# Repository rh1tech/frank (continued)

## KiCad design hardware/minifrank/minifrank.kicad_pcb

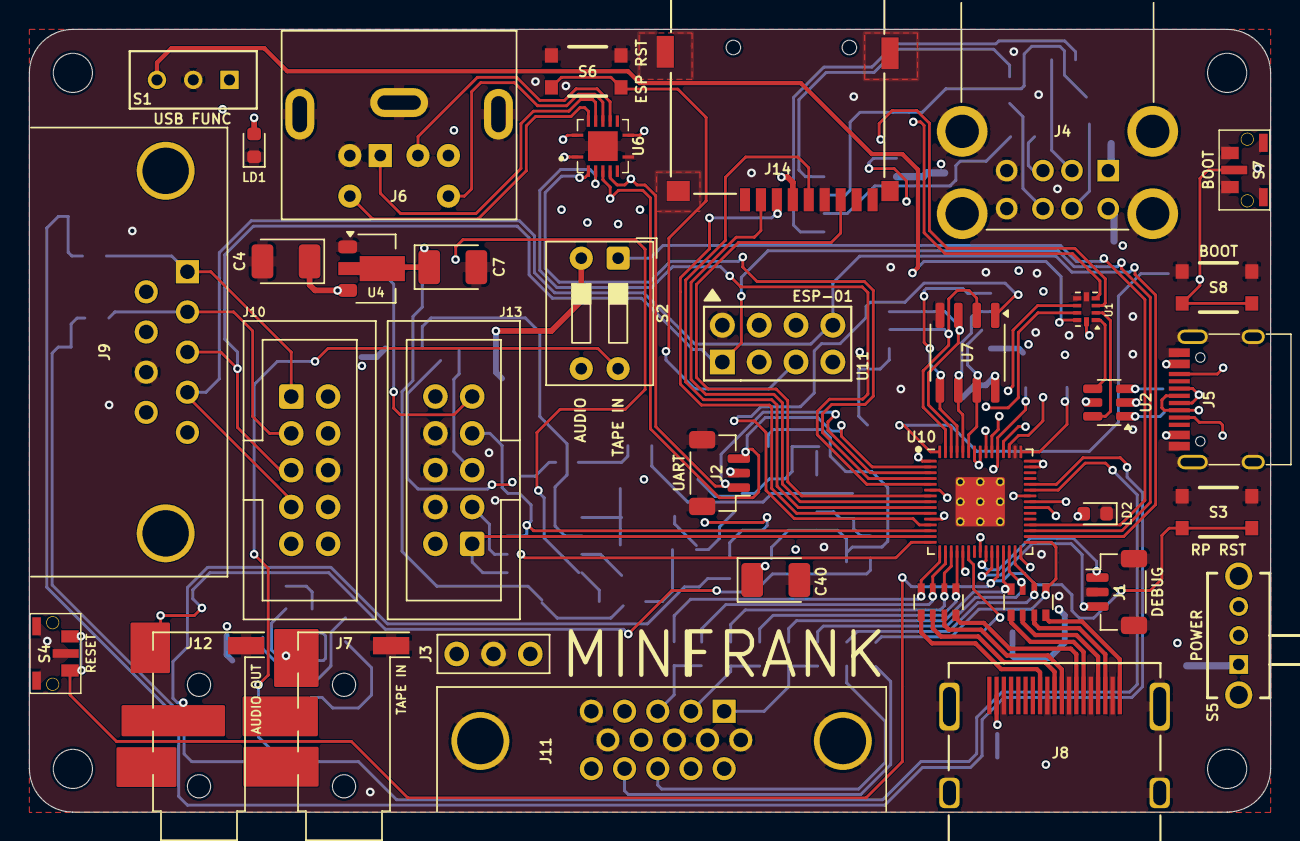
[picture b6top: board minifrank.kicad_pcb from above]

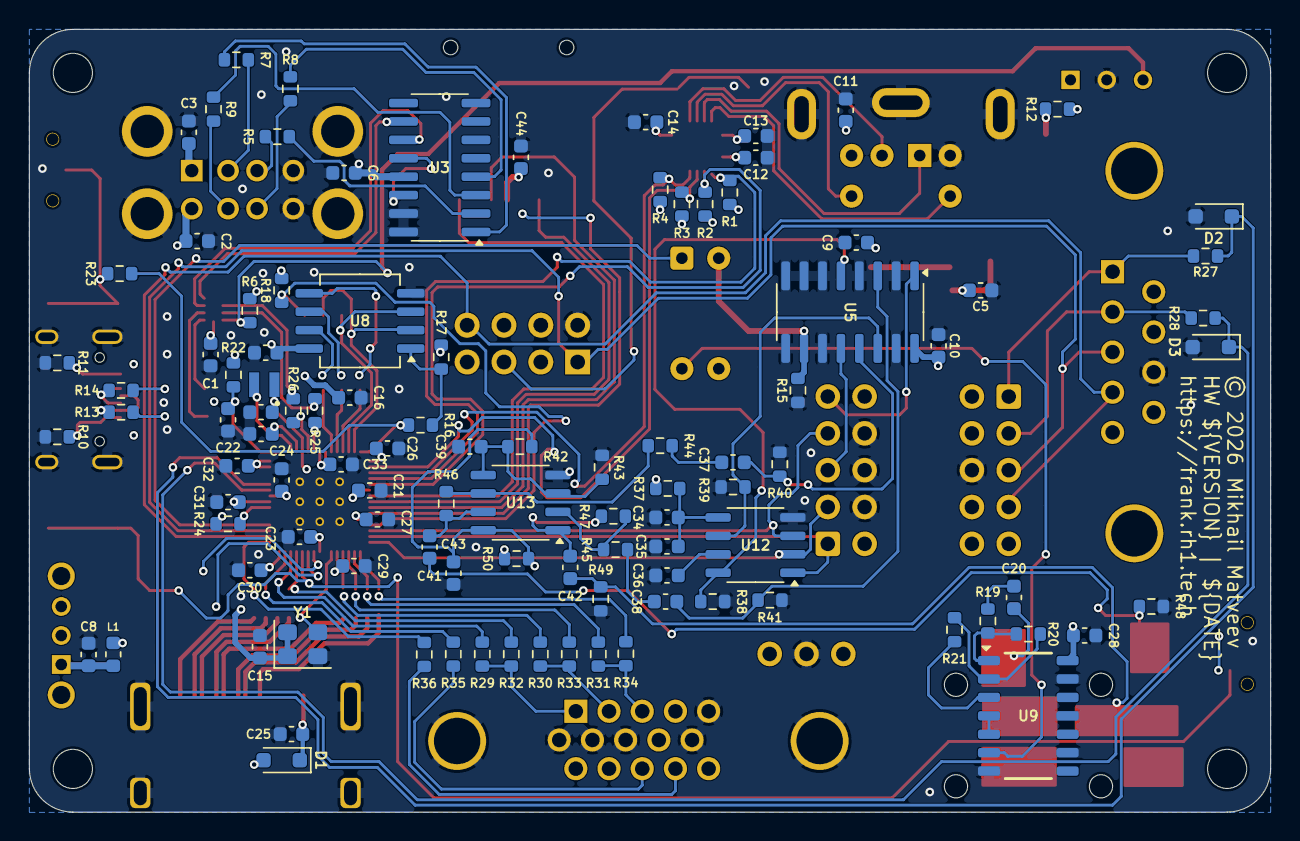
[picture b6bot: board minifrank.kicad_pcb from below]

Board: 4 copper layers, 85.6 x 54.0 mm, 143 parts (103 on the bottom side), 119 nets.

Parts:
C1, C5, C8, C9, C10, C11, C12, C13, C14, C15, C16, C17, C20, C21, C24, C25, C26, C27, C28, C29, C30, C31, C32, C33, C35, C43, C44: 100n; C_0603_1608Metric
C2, C3, C34, C36, C37, C38, C39, C41, C42: 10u; C_0603_1608Metric
C4, C7: 22u; CP_EIA-3528-12_Kemet-T
C6, C18, C19, C22, C23: 4.7u; C_0603_1608Metric
C40: 10u; CP_EIA-3528-12_Kemet-T
D1: 1N5819WS; D_SOD-323
D2, D3: 3V3; D_SOD-323
H1, H2, H3, H4: Hole 2.7mm; MountingHole_2.7mm
J1: DEBUG; JST_SH_BM03B-SRSS-TB_1x03-1MP_P1.00mm_Vertical
J2: UART; JST_SH_BM03B-SRSS-TB_1x03-1MP_P1.00mm_Vertical
J3: PWR; PinHeader_1x03_P2.54mm
J4: SS-52100-004; USB_A_Stacked
J5: USB4215-03-A; USB_C_Receptacle
J6: MDC-036; MiniDIN_6pin_Female
J7: PJ-320D; AudioJack_3.5mm_PJ320D_TapeIn
J8: HDMI-001 19PCBTP; HDMI_Female
J9: GP2; DSUB-9_Male_TopMount
J10: Conn_02x05_Top_Bottom; IDC-Header_2x05_P2.54mm_Vertical
J11: VGA; DSUB-15_Female
J12: PJ-320D; AudioJack_3.5mm_PJ320D_AudioOut
J13: Ext_Sound; IDC-Header_2x05_P2.54mm_Vertical
J14: 104031-0811; MicroSD_SMD_Long
L1: 330R; L_0603_1608Metric
L2: 3.3u; L_pol_2016
LD1: Green; LED_0603_1608Metric
LD2: Blue; LED_0603_1608Metric
R1, R2, R3, R4, R6, R15, R17, R18, R40, R41, R42, R43, R44, R45: 10K; R_0603_1608Metric
R5, R7, R8, R9, R13, R14: 22R; R_0603_1608Metric
R10, R11: 5.1K; R_0603_1608Metric
R12, R23, R24, R27, R28, R32, R33, R34: 1K; R_0603_1608Metric
R16: 0R; R_0603_1608Metric
R19: 4.7K; R_0603_1608Metric
R20, R21: 100K; R_0603_1608Metric
R22: 33R; R_0603_1608Metric
R25, R26: 27R; R_0603_1608Metric
R29, R30, R31: 330R; R_0603_1608Metric
R35, R36, R37, R50: 100R; R_0603_1608Metric
R38, R39: 470R; R_0603_1608Metric
R46, R47: 47K; R_0603_1608Metric
R48, R49: 20K; R_0603_1608Metric
RN1, RN2: 270R; R_Array_4x0603
S1: SS12D00; Switch_Slide_SS12D00
S2: SW_DIP_x02; SW_DIP_SPSTx02_Slide_9.78x7.26mm_W7.62mm_P2.54mm
S3, S8: RP Reset; KMR_2
S4, S7: RP Reset; TS-1234VW
S5: SK12D07VG3NS
S6: ESP Reset; KMR_2
U1: TS3USB221RSER; UQFN-10
U2: USBLC6-2SC6; SOT-23-6
U3: MW7211A; SOP-16
U4: AMS1117-3.3; SOT-89-3
U5: 74HC4052D; SOP-16_P1.27mm
U6: TXS0104ERGYR; RGY_S-PVQFN-N14_
U7: ESP-PSRAM64H; SO-8
U8: W25Q128JVS; SOIC-8
U9: CD4069UBM; SOIC127P600X175-14N
U10: RP2350; QFN-60_RP2350A
U11: ESP-01v090; ESP-01
U12: TDA1387T; SO-8
U13: LM358; SO-8
Y1: ASE-12MHz; Oscillator_SMD_Abracon_ASE-4Pin_3.2x2.5mm

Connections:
+1V1: C19.1, C21.1, C23.1, C24.1, L2.1, U10.6 (DVDD), U10.23 (DVDD), U10.39 (DVDD), U10.50 (VREG_FB)
+3V3: C1.2, C7.1, C9.2, C12.1, C14.1, C15.1, C16.1, C17.1, C18.1, C26.1, C27.1, C28.1, C29.1, C30.1, C31.1, C32.1, C33.1, C44.2, J3.1, J13.10, J14.4 (VDD), R1.2, R2.2, R3.2, R4.2, R6.1, R12.2, R17.1, R18.2, R22.1, U1.10 (VCC), U4.2 (VO), U6.1 (VCCA), U6.8 (OE), U7.8 (VCC), U8.8 (VCC), U9.14 (VDD), U10.1 (IOVDD), U10.11 (IOVDD), U10.20 (IOVDD), U10.30 (IOVDD), U10.38 (IOVDD), U10.44 (ADC_AVDD), U10.45 (IOVDD), U10.49 (VREG_VIN), U10.53 (USB_OTP_VDD), U10.54 (QSPI_IOVDD), U11.7 (VCC), Y1.1 (EN), Y1.4 (Vdd)
/Audio Multiplexer/AMP_IN_L: C37.1, R40.1, U5.13 (1Z)
/Audio Multiplexer/AMP_IN_R: C38.1, R41.1, U5.3 (2Z)
/Audio Multiplexer/AUDIOSW: R15.2, S2.2, U5.10 (S0)
/Audio Multiplexer/TDA_L: R39.2, U5.14 (1Y1), U12.6 (A_LEFT)
/Audio Multiplexer/TDA_R: R38.1, U5.5 (2Y1), U12.8 (A_RIGHT)
/Audio Multiplexer/TS_OUT_L: J13.3, U5.12 (1Y0)
/Audio Multiplexer/TS_OUT_R: J13.5, U5.1 (2Y0)
/Audio/AMP_OUTL: C41.2, J12.T, R48.2
/Audio/AMP_OUTR: C42.2, J12.R, R49.2
/D+: R25.1, U1.8 (D+)
/D-: R26.1, U1.7 (D-)
/ESP_RST: S6.2, S6.4, U11.5 (RST)
/GPIO0: J2.1, R3.1, U6.4 (A3), U10.2 (GPIO0)
/GPIO1: J2.3, R4.1, U6.5 (A4), U10.3 (GPIO1)
/GPIO2: R1.1, U6.2 (A1), U10.4 (GPIO2)
/GPIO3: R2.1, U6.3 (A2), U10.5 (GPIO3)
/GPIO4: J14.7 (DAT0), U10.7 (GPIO4)
/GPIO5: J14.2 (DAT3/CD), U10.8 (GPIO5)
/GPIO6: J14.5 (CLK), U10.9 (GPIO6)
/GPIO7: J14.3 (CMD), U10.10 (GPIO7)
/GPIO9: J13.4, U10.13 (GPIO9), U12.3 (DATA)
/GPIO10: J13.1, U10.14 (GPIO10), U12.1 (SCLK)
/GPIO11: J13.2, U10.15 (GPIO11), U12.2 (LRCK)
/GPIO12: R34.1, RN1.4 (R4.1), U10.16 (GPIO12)
/GPIO13: R31.1, RN1.3 (R3.1), U10.17 (GPIO13)
/GPIO14: R33.1, RN1.2 (R2.1), U10.18 (GPIO14)
/GPIO15: R30.1, RN1.1 (R1.1), U10.19 (GPIO15)
/GPIO16: R32.1, RN2.4 (R4.1), U10.27 (GPIO16)
/GPIO17: R29.1, RN2.3 (R3.1), U10.28 (GPIO17)
/GPIO18: R35.2, RN2.2 (R2.1), U10.29 (GPIO18)
/GPIO19: R36.2, RN2.1 (R1.1), U10.31 (GPIO19)
/GPIO20: J9.4, J10.4, U10.32 (GPIO20), U11.8 (URXD)
/GPIO21: J9.3, J10.3, U10.33 (GPIO21), U11.1 (UTXD)
/GPIO22: S2.1, U10.34 (GPIO22)
/GPIO26: D3.1 (K), R28.1, U10.40 (GPIO26_ADC0)
/GPIO27: D2.1 (K), R27.1, U10.41 (GPIO27_ADC1)
/Gamepad/G_DATA1: J9.2, J10.2, R28.2
/Gamepad/G_DATA2: J9.1, J10.1, R27.2
/PS2/KB_CLK_5V: J6.5, U6.13 (B1)
/PS2/KB_DATA_5V: J6.1, U6.12 (B2)
/PS2/MS_CLK_5V: J6.6, U6.11 (B3)
/PS2/MS_DATA_5V: J6.2, U6.10 (B4)
/Power/D1+: U1.1 (1D+), U2.4 (I/O2)
/Power/D1-: U1.2 (1D-), U2.6 (I/O1)
/Power/D2+: U1.3 (2D+), U3.11 (DPU)
/Power/D2-: U1.4 (2D-), U3.10 (DMU)
/Power/DS1+: R5.1, U3.2 (DP0)
/Power/DS1-: R7.1, U3.1 (DM0)
/Power/DS2+: R8.1, U3.4 (DP1)
/Power/DS2-: R9.1, U3.3 (DM1)
/Power/VBUS_IN: J5.2 (VBUS), J5.11 (VBUS), S5.2
/RP2350A/FLASH_SS: R16.2, R17.2, U8.1 (~CS)
/RP2350A/GPIO8: R18.1, U7.1 (~CE), U10.12 (GPIO8)
/RP2350A/QSPI_SCLK: U7.6 (SCLK), U8.6 (CLK), U10.56 (QSPI_SCLK)
/RP2350A/QSPI_SD0: U7.5 (SI/SIO), U8.5 (DI(IO0)), U10.57 (QSPI_SD0)
/RP2350A/QSPI_SD1: U7.2 (SO/SIO), U8.2 (DO(IO1)), U10.59 (QSPI_SD1)
/RP2350A/QSPI_SD2: U7.3 (SIO2), U8.3 (IO2), U10.58 (QSPI_SD2)
/RP2350A/QSPI_SD3: U7.7 (SIO3), U8.7 (IO3), U10.55 (QSPI_SD3)
/RP2350A/QSPI_SS: R16.1, R23.1, U10.60 (QSPI_SS)
/RP2350A/SWCLK: J1.3, U10.24 (SWCLK)
/RP2350A/SWD: J1.1, U10.25 (SWD)
/RP2350A/VREG_AVDD: C22.1, R22.2, U10.46 (VREG_AVDD)
/RP2350A/VREG_LX: L2.2, U10.48 (VREG_LX)
/RP2350A/XIN: U10.21 (XIN), Y1.3 (OUT)
/RP2350A/~USB_BOOT: R23.2, S7.2, S8.2, S8.4
/RUN: S3.2, S3.4, S4.1, U10.26 (RUN)
/Tape In/LOAD_IN: S2.4, U9.6 (I=*C)
/Tape In/TAPE: C20.2, J7.T
/USBSW: R6.2, S1.3, U1.9 (S)
GND: C1.1, C2.2, C3.2, C4.2, C5.1, C6.2, C7.2, C8.2, C9.1, C10.1, C11.2, C12.2, C13.2, C14.2, C15.2, C16.2, C17.2, C18.2, C19.2, C21.2, C22.2, C23.2, C24.2, C25.2, C26.2, C27.2, C28.2, C29.2, C30.2, C31.2, C32.2, C33.2, C34.2, C35.2, C36.2, C39.1, C40.2, C43.1, C44.1, D2.2 (A), D3.2 (A), J1.2, J2.2, J3.2, J4.4 (GND1), J4.8 (GND2), J4.SH (Shield), J5.1 (GND), J5.12 (GND), J5.13 (SHIELD), J6.3, J7.S, J8.2 (G_D2), J8.5 (G_D1), J8.8 (G_D0), J8.11 (G_CLK), J8.17 (G_DDC/CEC), J8.20 (SHIELD1), J8.21 (SHIELD2), J8.22 (SHIELD3), J8.23 (SHIELD4), J9.8, J10.8, J11.0, J11.5, J11.6, J11.7, J11.8, J11.10, J12.S, J13.7, J13.8, J13.9, J14.6 (VSS), LD1.1 (K), LD2.1 (K), R10.1, R11.1, R15.1, R38.2, R39.1, R40.2, R41.2, R43.1, R48.1, R49.1, S1.2, S3.1, S3.3, S4.2, S4.3 (GND), S6.1, S6.3, S7.1, S7.3 (GND), S8.1, S8.3, U1.5 (GND), U1.6 (~OE), U2.2 (GND), U3.15 (GND), U3.16 (GND), U4.1 (GND), U5.2 (2Y2), U5.4 (2Y3), U5.6 (~E), U5.7 (VEE), U5.8 (GND), U5.9 (S1), U5.11 (1Y3), U5.15 (1Y2), U6.7 (GND), U6.15 (THERMAL_PAD), U7.4 (VSS), U8.4 (GND), U9.7 (VSS), U9.9 (D14), U9.11 (E), U9.13 (F), U10.47 (VREG_PGND), U10.61 (GND), U11.2 (GND), U12.4 (AGND), U13.4 (V-), Y1.2 (GND)
GPIO25: R24.2, U10.37 (GPIO25)
unnamed: C8.1, L1.2, S5.1
unnamed: C20.1, R19.2
unnamed: C37.2, R44.2
unnamed: C38.2, R45.2
unnamed: C41.1, R46.1, U13.7
unnamed: C42.1, R47.1, U13.1
unnamed: C25.1, D1.1 (K), J8.18 (+5V)
unnamed: J4.3 (D1+), R5.2
unnamed: J4.2 (D1-), R7.2
unnamed: J4.7 (D2+), R8.2
unnamed: J4.6 (D2-), R9.2
unnamed: J5.4 (CC1), R10.2
unnamed: J5.10 (CC2), R11.2
unnamed: J5.5 (DN2), J5.7 (DN1), R13.2
unnamed: J5.6 (DP1), J5.8 (DP2), R14.2
unnamed: J8.12 (CLKN), RN1.5 (R4.2)
unnamed: J8.10 (CLKP), RN1.6 (R3.2)
unnamed: J8.9 (D0N), RN1.7 (R2.2)
unnamed: J8.7 (D0P), RN1.8 (R1.2)
unnamed: J8.6 (D1N), RN2.5 (R4.2)
unnamed: J8.4 (D1P), RN2.6 (R3.2)
unnamed: J8.3 (D2N), RN2.7 (R2.2)
unnamed: J8.1 (D2P), RN2.8 (R1.2)
unnamed: J11.1, R29.2, R32.2
unnamed: J11.2, R30.2, R33.2
unnamed: J11.3, R31.2, R34.2
unnamed: J11.13, R35.1
unnamed: J11.14, R36.1
unnamed: LD1.2 (A), R12.1
unnamed: LD2.2 (A), R24.1
unnamed: R13.1, U2.1 (I/O1)
unnamed: R14.1, U2.3 (I/O2)
unnamed: U3.12 (VD33), U3.14 (VD3)
unnamed: R19.1, R20.2, U9.1 (A)
unnamed: R21.1, U9.3 (B)
unnamed: U9.4 (H=*B), U9.5 (C)
unnamed: R20.1, R21.2, U9.2 (G-*A)
unnamed: R26.2, U10.51 (USB_DM)
unnamed: R25.2, U10.52 (USB_DP)
unnamed: C36.1, U12.7 (FLT)
unnamed: C34.1, C35.1, R37.1, U12.5 (VA)
unnamed: C39.2, R42.1, R43.2, U13.3 (+), U13.5 (+)
unnamed: R45.1, R47.2, U13.2 (-)
unnamed: R44.1, R46.2, U13.6 (-)
unnamed: C40.1, C43.2, R42.2, R50.2, U13.8 (V+)
VBUS: C2.1, C3.1, C4.1, C5.2, C6.1, C10.2, C11.1, C13.1, D1.2 (A), J3.3, J4.1 (VBUS1), J4.5 (VBUS2), J6.4, J9.6, J10.6, J13.6, L1.1, R37.2, R50.1, S2.3, U2.5 (VBUS), U3.13 (VDD5), U4.3 (VI), U5.16 (VCC), U6.14 (VCCB)

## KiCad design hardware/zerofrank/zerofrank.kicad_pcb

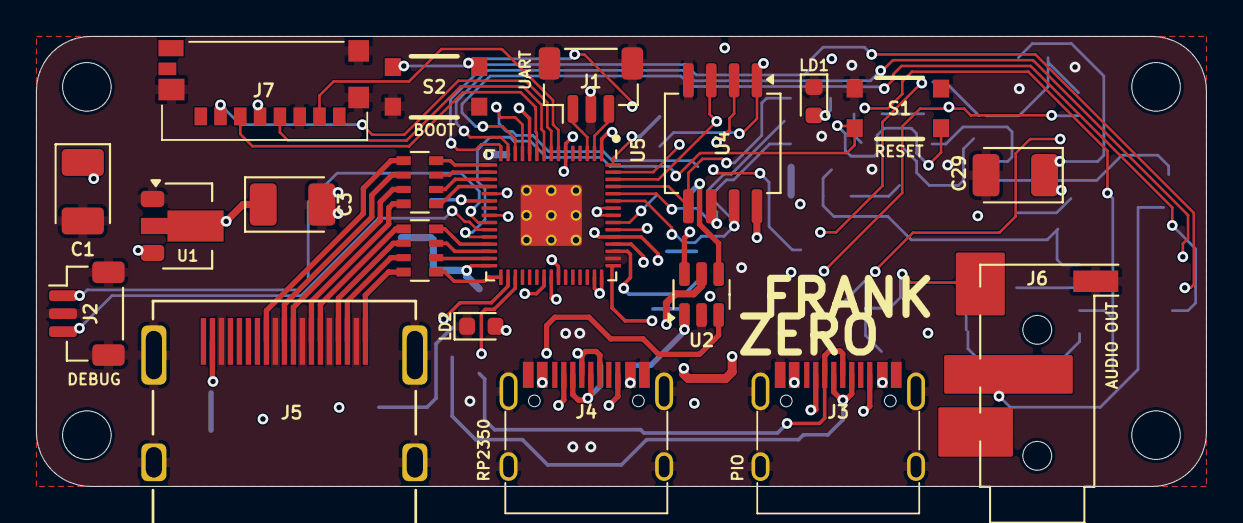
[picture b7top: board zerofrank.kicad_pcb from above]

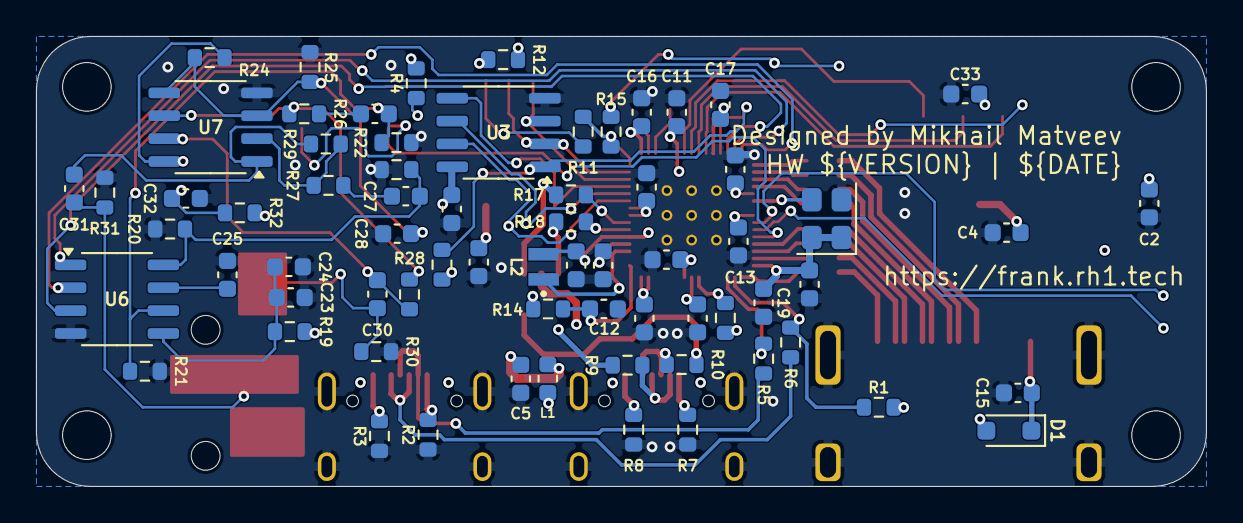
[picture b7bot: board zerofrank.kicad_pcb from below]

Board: 4 copper layers, 65.0 x 25.0 mm, 93 parts (69 on the bottom side), 79 nets.

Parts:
C1, C3: 22u; CP_Tantalum_3528-12
C2, C4, C5, C6, C7, C8, C11, C14, C15, C16, C17, C18, C19, C20, C21, C22, C24, C32, C33: 100n; C_0603_1608Metric
C9, C10, C12, C13: 4.7u; C_0603_1608Metric
C23, C25, C26, C27, C28, C30, C31: 10u; C_0603_1608Metric
C29: 10u; CP_Tantalum_3528-12
D1: 1N5819WS; D_SOD-323
H1, H2, H3, H4: Hole 2.7mm; MountingHole_2.7mm
J1: UART; JST_SH_1x03_P1.00mm_Vertical
J2: DEBUG; JST_SH_1x03_P1.00mm_Vertical
J3, J4: USB4215-03-A; USB_C_Receptacle
J5: HDMI-001 19PCBTP; HDMI_Female
J6: PJ-320D; AudioJack_3.5mm_PJ320D_AudioOut
J7: 0475710001; MicroSD_SMD_Short
L1: 330R; L_0603_1608Metric
L2: 3.3u; L_pol_2016
LD1: Green; LED_0603_1608Metric
LD2: Blue; LED_0603_1608Metric
R1: 1.5K; R_0603_1608Metric
R2, R3, R7, R8: 5.1K; R_0603_1608Metric
R4, R15, R16: 1K; R_0603_1608Metric
R5, R6, R9, R10: 22R; R_0603_1608Metric
R11: 0R; R_0603_1608Metric
R12, R13, R22, R23, R24, R25, R26, R27: 10K; R_0603_1608Metric
R14: 33R; R_0603_1608Metric
R17, R18: 27R; R_0603_1608Metric
R19, R32: 100R; R_0603_1608Metric
R20, R21: 470R; R_0603_1608Metric
R28, R29: 47K; R_0603_1608Metric
R30, R31: 20K; R_0603_1608Metric
RN1, RN2: 270R; R_Array_4x0603
S1, S2: RP Reset; KMR_2
U1: AMS1117-3.3; SOT-89-3
U2: USBLC6-2SC6; SOT-23-6
U3: ESP-PSRAM64H; SO-8
U4: W25Q128JVS; SOIC-8
U5: RP2350; QFN-60_RP2350A
U6: TDA1387T; SO-8
U7: LM358; SO-8
Y1: ASE-12MHz; Oscillator_SMD_4Pin_3.2x2.5mm

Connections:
+1V1: C10.1, C11.1, C13.1, C14.1, L2.1, U5.6 (DVDD), U5.23 (DVDD), U5.39 (DVDD), U5.50 (VREG_FB)
+3V3: C3.1, C4.2, C6.1, C7.1, C8.1, C9.1, C16.1, C17.1, C18.1, C19.1, C20.1, C21.1, C22.1, C33.2, J7.P4 (VDD), R1.2, R4.2, R12.1, R13.2, R14.1, U1.2 (VO), U3.8 (VCC), U4.8 (VCC), U5.1 (IOVDD), U5.11 (IOVDD), U5.20 (IOVDD), U5.30 (IOVDD), U5.38 (IOVDD), U5.44 (ADC_AVDD), U5.45 (IOVDD), U5.49 (VREG_VIN), U5.53 (USB_OTP_VDD), U5.54 (QSPI_IOVDD), Y1.1 (EN), Y1.4 (Vdd)
/Audio/AMP_OUTL: C30.2, J6.T, R30.2
/Audio/AMP_OUTR: C31.2, J6.R, R31.2
/Audio/TDA_L: C26.1, R21.2, R22.1, U6.6 (A_LEFT)
/Audio/TDA_R: C27.1, R20.1, R23.1, U6.8 (A_RIGHT)
/D+: R17.1, U2.4 (I/O2)
/D-: R18.1, U2.6 (I/O1)
/GPIO4: J7.P7 (DAT0), U5.7 (GPIO4)
/GPIO5: J7.P2 (CD/DAT3), U5.8 (GPIO5)
/GPIO6: J7.P5 (CLK), U5.9 (GPIO6)
/GPIO7: J7.P3 (CMD), U5.10 (GPIO7)
/GPIO9: U5.13 (GPIO9), U6.3 (DATA)
/GPIO10: U5.14 (GPIO10), U6.1 (SCLK)
/GPIO11: U5.15 (GPIO11), U6.2 (LRCK)
/GPIO12: RN1.4 (R4.1), U5.16 (GPIO12)
/GPIO13: RN1.3 (R3.1), U5.17 (GPIO13)
/GPIO14: RN1.2 (R2.1), U5.18 (GPIO14)
/GPIO15: RN1.1 (R1.1), U5.19 (GPIO15)
/GPIO16: RN2.4 (R4.1), U5.27 (GPIO16)
/GPIO17: RN2.3 (R3.1), U5.28 (GPIO17)
/GPIO18: RN2.2 (R2.1), U5.29 (GPIO18)
/GPIO19: RN2.1 (R1.1), U5.31 (GPIO19)
/PIO_D+: R1.1, R6.1, U5.32 (GPIO20)
/PIO_D-: R5.1, U5.33 (GPIO21)
/Power/VBUS_IN: C5.1, J3.2 (VBUS), J3.11 (VBUS), J4.2 (VBUS), J4.11 (VBUS), L1.2
/RP2350A/FLASH_SS: R11.2, R12.2, U4.1 (~CS)
/RP2350A/GPIO0: J1.1, U5.2 (GPIO0)
/RP2350A/GPIO1: J1.3, U5.3 (GPIO1)
/RP2350A/GPIO8: R13.1, U3.1 (~CE), U5.12 (GPIO8)
/RP2350A/QSPI_SCLK: U3.6 (SCLK), U4.6 (CLK), U5.56 (QSPI_SCLK)
/RP2350A/QSPI_SD0: U3.5 (SI/SIO), U4.5 (DI(IO0)), U5.57 (QSPI_SD0)
/RP2350A/QSPI_SD1: U3.2 (SO/SIO), U4.2 (DO(IO1)), U5.59 (QSPI_SD1)
/RP2350A/QSPI_SD2: U3.3 (SIO2), U4.3 (IO2), U5.58 (QSPI_SD2)
/RP2350A/QSPI_SD3: U3.7 (SIO3), U4.7 (IO3), U5.55 (QSPI_SD3)
/RP2350A/QSPI_SS: R11.1, R15.1, U5.60 (QSPI_SS)
/RP2350A/SWCLK: J2.3, U5.24 (SWCLK)
/RP2350A/SWD: J2.1, U5.25 (SWD)
/RP2350A/VREG_AVDD: C12.1, R14.2, U5.46 (VREG_AVDD)
/RP2350A/VREG_LX: L2.2, U5.48 (VREG_LX)
/RP2350A/XIN: U5.21 (XIN), Y1.3 (OUT)
/RP2350A/~USB_BOOT: R15.2, S2.2, S2.4
/RUN: S1.2, S1.4, U5.26 (RUN)
GND: C1.2, C2.1, C3.2, C4.1, C5.2, C6.2, C7.2, C8.2, C9.2, C10.2, C11.2, C12.2, C13.2, C14.2, C15.2, C16.2, C17.2, C18.2, C19.2, C20.2, C21.2, C22.2, C23.2, C24.2, C25.2, C28.1, C29.2, C32.1, C33.1, J1.2, J2.2, J3.1 (GND), J3.12 (GND), J3.13 (SHIELD), J4.1 (GND), J4.12 (GND), J4.13 (SHIELD), J5.2 (G_D2), J5.5 (G_D1), J5.8 (G_D0), J5.11 (G_CLK), J5.17 (G_DDC/CEC), J5.20 (SHIELD1), J5.21 (SHIELD2), J5.22 (SHIELD3), J5.23 (SHIELD4), J6.S, J7.P6 (VSS), J7.SH (GND_1), LD1.1 (K), LD2.1 (K), R2.1, R3.1, R7.1, R8.1, R20.2, R21.1, R22.2, R23.2, R25.1, R30.1, R31.1, S1.1, S1.3, S2.1, S2.3, U1.1 (GND), U2.2 (GND), U3.4 (VSS), U4.4 (GND), U5.47 (VREG_PGND), U5.61 (GND), U6.4 (AGND), U7.4 (V-), Y1.2 (GND)
GPIO25: R16.2, U5.37 (GPIO25)
unnamed: C26.2, R26.2
unnamed: C27.2, R27.2
unnamed: C30.1, R28.1, U7.7
unnamed: C31.1, R29.1, U7.1
unnamed: C15.1, D1.1 (K), J5.18 (+5V)
unnamed: J3.4 (CC1), R2.2
unnamed: J3.10 (CC2), R3.2
unnamed: J3.5 (DN2), J3.7 (DN1), R5.2
unnamed: J3.6 (DP1), J3.8 (DP2), R6.2
unnamed: J4.4 (CC1), R7.2
unnamed: J4.10 (CC2), R8.2
unnamed: J4.5 (DN2), J4.7 (DN1), R9.2
unnamed: J4.6 (DP1), J4.8 (DP2), R10.2
unnamed: J5.12 (CLKN), RN1.5 (R4.2)
unnamed: J5.10 (CLKP), RN1.6 (R3.2)
unnamed: J5.9 (D0N), RN1.7 (R2.2)
unnamed: J5.7 (D0P), RN1.8 (R1.2)
unnamed: J5.6 (D1N), RN2.5 (R4.2)
unnamed: J5.4 (D1P), RN2.6 (R3.2)
unnamed: J5.3 (D2N), RN2.7 (R2.2)
unnamed: J5.1 (D2P), RN2.8 (R1.2)
unnamed: LD1.2 (A), R4.1
unnamed: LD2.2 (A), R16.1
unnamed: R9.1, U2.1 (I/O1)
unnamed: R10.1, U2.3 (I/O2)
unnamed: R18.2, U5.51 (USB_DM)
unnamed: R17.2, U5.52 (USB_DP)
unnamed: C25.1, U6.7 (FLT)
unnamed: C23.1, C24.1, R19.1, U6.5 (VA)
unnamed: C28.2, R24.1, R25.2, U7.3 (+), U7.5 (+)
unnamed: R27.1, R29.2, U7.2 (-)
unnamed: R26.1, R28.2, U7.6 (-)
unnamed: C29.1, C32.2, R24.2, R32.2, U7.8 (V+)
VBUS: C1.1, C2.2, D1.2 (A), L1.1, R19.2, R32.1, U1.3 (VI), U2.5 (VBUS)

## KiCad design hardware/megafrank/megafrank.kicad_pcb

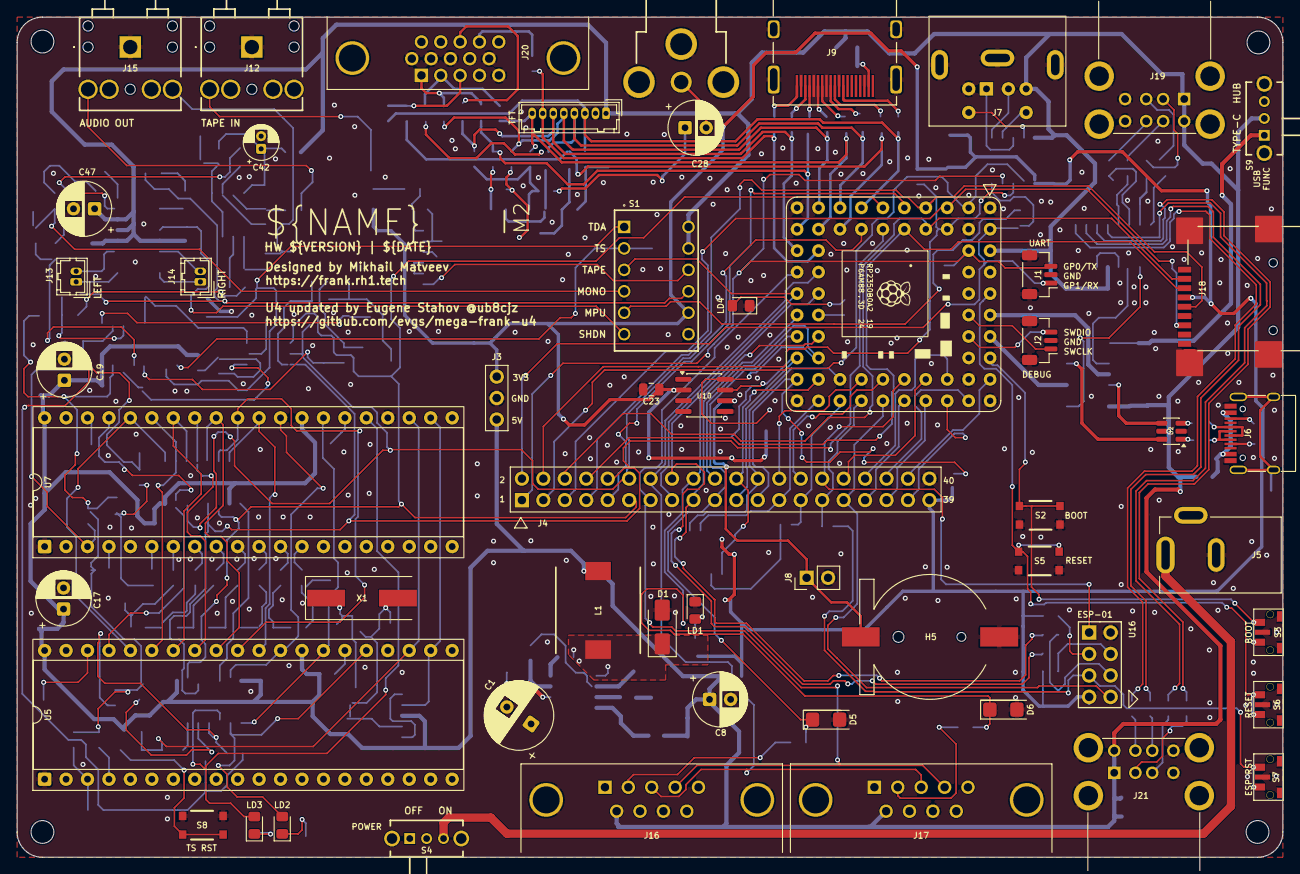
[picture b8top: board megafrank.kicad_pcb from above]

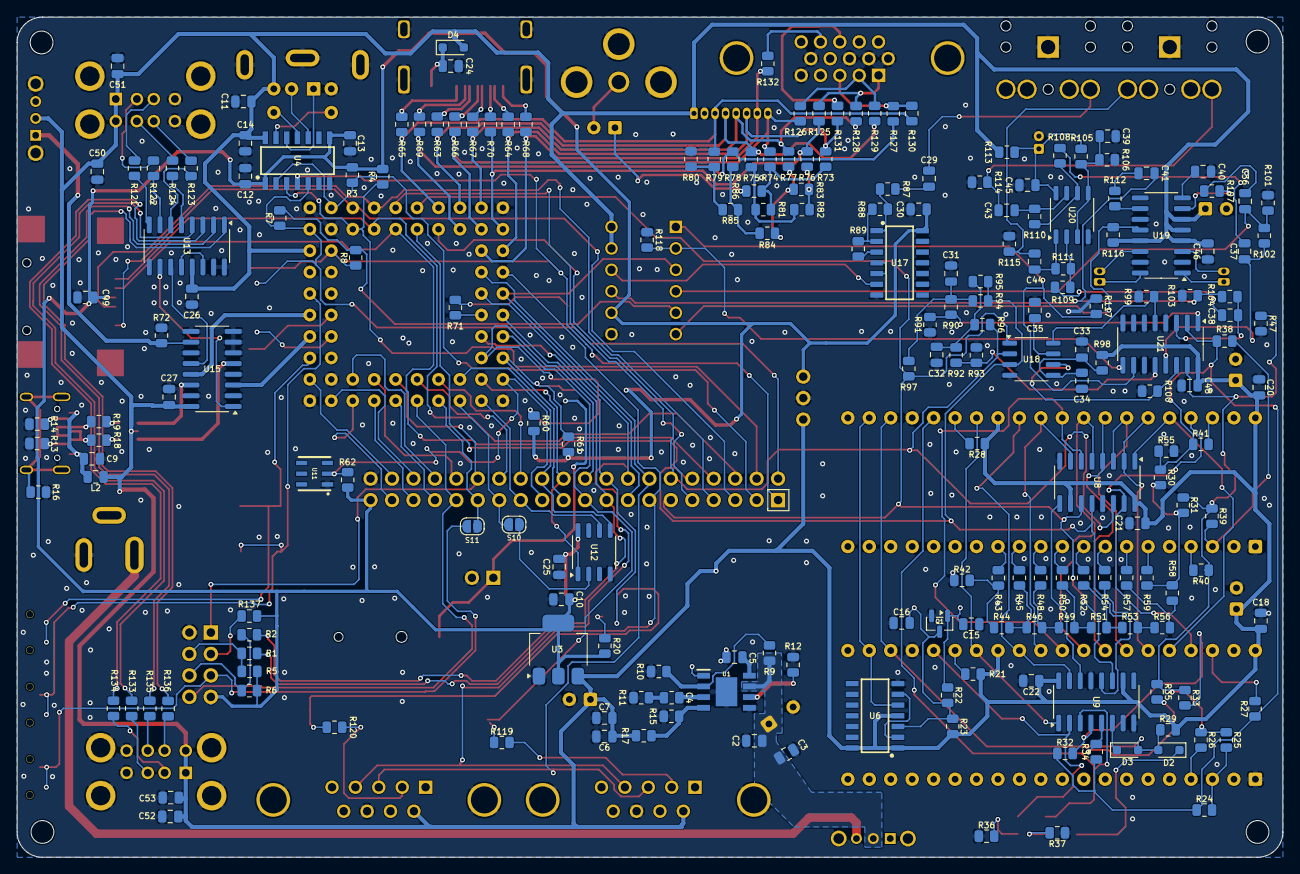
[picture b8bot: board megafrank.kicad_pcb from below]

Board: 2 copper layers, 149.9 x 99.5 mm, 262 parts (204 on the bottom side), 223 nets.

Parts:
C1: 680u; C_Radial_D8.0mm_P3.50mm
C2, C7, C10, C33, C35, C37, C38, C39, C43, C44, C50, C51, C52, C53: 10u; C_0805_2012Metric
C3, C5, C6, C9, C11, C12, C13, C14, C18, C20, C21, C22, C23, C24, C25, C27, C29, C30, C34, C40, C45, C48, C49: 100n; C_0805_2012Metric
C4: 150pF; R_0805_2012Metric
C8, C28: 220u; C_Radial_D6.3mm_P2.50mm
C15, C16: 22p; C_0805_2012Metric
C17, C19, C47: 100u; C_Radial_D6.3mm_P2.50mm
C26: 4.7u; C_0805_2012Metric
C31, C32: 47n; C_0805_2012Metric
C36, C41, C46: 1u; C_0805_2012Metric
C42: 10u; CP_Radial_D4.0mm_P1.50mm
D1: 1N5822; D_SMA
D2, D3: 1N4148; D_SOD-323
D4: 1N5819WS; D_SOD-323
D5, D6: 3V3; D_MiniMELF
H1, H2, H3, H4: Hole 2.7mm; MountingHole_2.7mm
H5: Battery_CR1220
J1: UART; JST_SH_1x03_P1.00mm_Vertical
J2: DEBUG; JST_SH_1x03_P1.00mm_Vertical
J3: PWR; PinHeader_1x03_P2.54mm
J4: Conn_02x20_Odd_Even; PinHeader_2x20_P2.54mm_Vertical
J5: DC-005-5A-2.0; BarrelJack_DC-005
J6: USB4215-03-A; USB_C_Receptacle
J7: MDC-036; MiniDIN_6pin_Female
J8: BAT 3V; PinHeader_1x02_P2.54mm_Vertical
J9: HDMI-001 19PCBTP; HDMI_Female
J10: RCA-103; BarrelJack_RCJ-012
J11: Pin Header 1x08; JST_GH_1x08_P1.25mm
J12, J15: SJ1-3525N; AudioJack_3.5mm_SJ1-3525N
J13: PAM L; JST_GH_1x02_P1.25mm
J14: PAM R; JST_GH_1x02_P1.25mm
J16, J17: GP2; DSUB-9_Male_TopMount
J18: 104031-0811; MicroSD_SMD_Long
J19, J21: SS-52100-004; USB_A_Stacked
J20: VGA; DSUB-15_Female
L1: 22uH; Inductor_CDRH104RNP
L2: 330R; C_0805_2012Metric
LD1: Green; LED_0805
LD2, LD3: Orange; LED_0805
LD4: Blue; LED_0805
Q1: BC850; SOT-23
R1, R2, R20, R21, R23, R28, R36, R37, R71, R96, R97, R119, R120, R128, R129, R130: 1K; R_0805_2012Metric
R3, R4, R5, R6, R7, R8, R29, R30, R31, R32, R33, R34, R35, R44, R46, R49, R51, R53, R56, R58, R72, R90, R92, R101, R102, R103, R104, R105, R106, R107, R108, R109, R112, R116, R117, R118, R137: 10K; R_0805_2012Metric
R9, R11, R12, R22, R88, R89: 100K; R_0805_2012Metric
R10: 24K; R_0805_2012Metric
R13, R14: 5.1K; R_0805_2012Metric
R15: 8.2K; R_0805_2012Metric
R16: 1M; R_0805_2012Metric
R17: 43K; R_0805_2012Metric
R18, R19, R121, R122, R123, R124, R133, R134, R135, R136: 22R; R_0805_2012Metric
R24, R25, R38, R39, R60, R61, R62, R87: 4.7K; R_0805_2012Metric
R26, R27, R40, R41, R91, R93, R94, R95: 2K; R_0805_2012Metric
R42, R43, R45, R48, R50, R52, R54, R57, R59, R114, R115: 20K; R_0805_2012Metric
R47, R55: 120R; R_0805_2012Metric
R63, R64, R65, R66, R67, R68, R69, R70, R74, R75, R76, R77, R78, R79: 270R; R_0805_2012Metric
R73: 750R; R_0805_2012Metric
R80: 300R; R_0805_2012Metric
R81, R82, R83, R84, R85: 150R; R_0805_2012Metric
R86: 51R; R_0805_2012Metric
R98, R113, R131, R132: 100R; R_0805_2012Metric
R99, R100: 470R; R_0805_2012Metric
R110, R111: 47K; R_0805_2012Metric
R125, R126, R127: 330R; R_0805_2012Metric
S1: DS01-254-S-06BE
S2: RP BOOT; Button_SMD_3x4x2mm
S3: RP BOOT; Button_SMD_TS1234VW
S4, S9: SK12D07VG3NS; Switch_Slide_SK12D07VG3NS
S5: RP Reset; Button_SMD_3x4x2mm
S6: RP Reset; Button_SMD_TS1234VW
S7: ESP Reset; Button_SMD_TS1234VW
S8: TS Reset; Button_SMD_3x4x2mm
S10: PSRAM On; SolderJumper-2_P1.3mm_Open_RoundedPad1.0x1.5mm
S11: PICO-ESP-RESET; SolderJumper-2_P1.3mm_Open_RoundedPad1.0x1.5mm
U1: MP1584EN-LF-Z; SOIC-9_P1.27mm
U2: USBLC6-2SC6; SOT-23-6
U3: AMS1117 3.3; SOT-223-3_TabPin2
U4: TXS0104EDR; SOIC-14_P1.27mm
U5, U7: JFC95101; DIP-40_W15.24mm_Socket
U6: 74HC74; SOIC-14_P1.27mm
U8, U9: 74HC595; SOP-16_P1.27mm
U10: DS3231MZ; SOIC-8_3.9x4.9mm_P1.27mm
U11: DS2401P+; TSOC-6
U12: ESP-PSRAM64; SO-8
U13: MW7211A; SOP-16_P1.27mm
U14: Pimoroni PGA2350; PGA2350
U15, U21: 74HC4052D; SOP-16_P1.27mm
U16: ESP-01v090; ESP-01S
U17: CD4069UBM; SOIC-14_P1.27mm
U18: TDA1387T; SO-8
U19: PAM8403D; SOP-16_P1.27mm
U20: LM358; SO-8
X1: 3.58 MHz; Crystal_HC49-S

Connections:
+3V3: C10.1, C12.1, C13.1, C23.1, C25.1, C30.1, C49.2, J3.1, J4.39, J18.4 (VDD), R3.2, R4.2, R5.2, R6.2, R20.2, R60.2, R61.2, R62.1, R137.2, S1.11, U3.2 (VO), U4.1 (VCCA), U4.8 (OE), U10.2 (VCC), U12.8 (VCC), U16.7 (VCC), U17.14 (VDD)
/Audio Multiplexer/AMP_IN_L: C37.1, R102.1, U21.13 (1Z)
/Audio Multiplexer/AMP_IN_R: C38.1, R104.1, U21.3 (2Z)
/Audio Multiplexer/PWM_OUT_L: R92.2, R93.1, U21.12 (1Y0)
/Audio Multiplexer/PWM_OUT_R: R90.2, R91.1, U21.1 (2Y0)
/Audio Multiplexer/SW_TDA: R117.2, S1.1, U21.10 (S0)
/Audio Multiplexer/SW_TS: R118.2, S1.2, U21.9 (S1)
/Audio Multiplexer/TDA_L: R100.2, U18.6 (A_LEFT), U21.14 (1Y1)
/Audio Multiplexer/TDA_R: R99.1, U18.8 (A_RIGHT), U21.5 (2Y1)
/Audio/AMP_OUTL: C43.2, J15.2 (TIP), R114.2
/Audio/AMP_OUTR: C44.2, J15.3 (RING), R115.2
/Audio/AMP_PAM_OUTL_M: J13.2, U19.3 (-OUTL)
/Audio/AMP_PAM_OUTL_P: J13.1, U19.1 (+OUT_L)
/Audio/AMP_PAM_OUTR_M: J14.2, U19.14 (-OUT_R)
/Audio/AMP_PAM_OUTR_P: J14.1, U19.16 (+OUT_R)
/Audio/TS/A1: R26.2, U5.4 (B)
/Audio/TS/A2: R40.2, U7.4 (B)
/Audio/TS/B1: R24.2, R25.2, U5.3 (A)
/Audio/TS/B2: R38.2, R39.2, U7.3 (A)
/Audio/TS/BEEP: R32.2, R33.2, U9.4 (QE)
/Audio/TS/C1: R27.2, U5.38 (C)
/Audio/TS/C2: R41.2, U7.38 (C)
/Audio/TS/CLK_1.75M: U5.22 (CLOCK), U6.5 (Q), U7.22 (CLOCK)
/Audio/TS/COVOX_OUT: R30.2, R31.2, R58.2, R59.1
/Audio/TS/DA0: U5.37 (DA0), U7.37 (DA0), U8.15 (QA)
/Audio/TS/DA1: U5.36 (DA1), U7.36 (DA1), U8.1 (QB)
/Audio/TS/DA2: U5.35 (DA2), U7.35 (DA2), U8.2 (QC)
/Audio/TS/DA3: U5.34 (DA3), U7.34 (DA3), U8.3 (QD)
/Audio/TS/DA4: U5.33 (DA4), U7.33 (DA4), U8.4 (QE)
/Audio/TS/DA5: U5.32 (DA5), U7.32 (DA5), U8.5 (QF)
/Audio/TS/DA6: U5.31 (DA6), U7.31 (DA6), U8.6 (QG)
/Audio/TS/DA7: U5.30 (DA7), U7.30 (DA7), U8.7 (QH)
/Audio/TS/DAC0: R43.2, U7.13 (IOB0)
/Audio/TS/DAC1: R45.2, U7.12 (IOB1)
/Audio/TS/DAC2: R48.2, U7.11 (IOB2)
/Audio/TS/DAC3: R50.2, U7.10 (IOB3)
/Audio/TS/DAC4: R52.2, U7.9 (IOB4)
/Audio/TS/DAC5: R54.2, U7.8 (IOB5)
/Audio/TS/DAC6: R57.2, U7.7 (IOB6)
/Audio/TS/DAC7: R59.2, U7.6 (IOB7)
/Audio/TS/L_IN: R25.1, R26.1, R31.1, R33.1, R35.1, R39.1, R40.1, R47.1, U21.15 (1Y2)
/Audio/TS/R_IN: R24.1, R27.1, R30.1, R32.1, R34.1, R38.1, R41.1, R55.1, U21.2 (2Y2)
/Audio/TS/SAVE: R34.2, R35.2, U9.5 (QF)
/Audio/TS/YM_BC1: U5.29 (BC1), U7.29 (BC1), U9.15 (QA)
/Audio/TS/YM_BDIR: U5.27 (BDIR), U7.27 (BDIR), U9.1 (QB)
/Audio/TS/YM_CS1: LD2.2 (A), U5.25 (A8), U9.2 (QC)
/Audio/TS/YM_CS2: LD3.2 (A), U7.25 (A8), U9.3 (QD)
/Audio/TS/YM_RST: D2.2 (A), D3.2 (A), R29.1, U5.23 (~RESET), U7.23 (~RESET)
/Audio/TS/YM_SEL1: R21.2, U5.26 (~SEL)
/Audio/TS/YM_SEL2: R28.2, U7.26 (~SEL)
/Composite/CVBS: C28.2, J10.1
/ESP01S/CH_PD: R137.1, U16.3 (CH_PD)
/ESP01S/GPIO0: R2.1, R6.1, U16.6 (GPIO0)
/ESP01S/GPIO2: R1.1, R5.1, U16.4 (GPIO2)
/ESPRST: S7.1, S11.1 (A), U16.5 (RST)
/MONO_L: C36.1, R101.1, R102.2, S1.4
/MONO_R: C41.1, R103.1, R104.2, S1.10
/MSPUP3V3: R7.2, R8.2, S1.5
/PBOOTSEL: S2.1, S2.3, S3.1, U14.51 (BOOTSEL)
/PGPIO0: J1.1, J4.1, R8.1, U4.4 (A3), U14.61 (GP0)
/PGPIO1: J1.3, J4.2, R7.1, U4.5 (A4), U14.62 (GP1)
/PGPIO2: J4.3, R3.1, U4.2 (A1), U14.2 (GP2)
/PGPIO3: J4.4, R4.1, U4.3 (A2), U14.3 (GP3)
/PGPIO4: J4.5, J18.7 (DAT0), U14.4 (GP4)
/PGPIO5: J4.6, J18.2 (DAT3/CD), U14.5 (GP5)
/PGPIO6: J4.7, J18.5 (CLK), U14.6 (GP6)
/PGPIO7: J4.8, J18.3 (CMD), U14.7 (GP7)
/PGPIO8: J4.9, U14.8 (GP8)
/PGPIO9: J4.10, R94.1, R95.1, U8.12 (RCLK), U9.12 (RCLK), U14.9 (GP9), U18.3 (DATA)
/PGPIO10: J4.11, R97.2, U8.11 (SRCLK), U9.11 (SRCLK), U14.10 (GP10), U18.1 (SCLK)
/PGPIO11: J4.12, R96.2, U8.14 (SER), U14.11 (GP11), U18.2 (LRCK)
/PGPIO12: J11.3, R65.2, R79.1, R130.1, U14.12 (GP12)
/PGPIO13: R69.2, R78.1, R127.1, U14.13 (GP13)
/PGPIO14: J11.4, R63.2, R75.1, R129.1, U14.14 (GP14)
/PGPIO15: J11.8, R66.2, R74.1, R126.1, U14.15 (GP15)
/PGPIO16: J11.5, R67.2, R77.1, R128.1, U14.16 (GP16)
/PGPIO17: R70.2, R76.1, R125.1, U14.17 (GP17)
/PGPIO18: J11.6, R64.2, R73.1, R131.2, U14.19 (GP18)
/PGPIO19: J11.7, R68.2, R132.2, U14.20 (GP19)
/PGPIO20: J4.13, J16.4, J17.4, U14.21 (GP20)
/PGPIO21: J4.14, J16.3, J17.3, U14.22 (GP21)
/PGPIO22: J4.15, S1.3, U14.23 (GP22)
/PGPIO23: J4.16, R1.2, U14.24 (GP23)
/PGPIO24: J4.17, R2.2, U14.25 (GP24)
/PGPIO26: D5.1 (K), J4.19, R119.1, U14.27 (GP26)
/PGPIO27: D6.1 (K), J4.18, R120.1, U14.28 (GP27)
/PGPIO28: J4.21, R61.1, U10.7 (SDA), U14.29 (GP28)
/PGPIO29: J4.20, R60.1, U10.8 (SCL), U14.30 (GP29)
/PGPIO30: J4.23, R62.2, U11.2 (DATA), U14.31 (GP30)
/PGPIO31: J4.22, U12.1 (~CE), U14.32 (GP31)
/PGPIO32: J4.25, U12.6 (SCLK), U14.34 (GP32)
/PGPIO33: J4.24, U12.5 (SI/SIO), U14.35 (GP33)
/PGPIO34: J4.27, S10.2 (B), U14.36 (GP34)
/PGPIO35: J4.26, U14.37 (GP35)
/PGPIO36: J4.29, S11.2 (B), U14.38 (GP36)
/PGPIO37: J4.28, U14.39 (GP37)
/PGPIO38: J4.31, U14.40 (GP38), U16.8 (URXD)
/PGPIO39: J4.30, U14.41 (GP39), U16.1 (UTXD)
/PGPIO40: J4.33, U14.42 (GP40)
/PGPIO41: J4.32, U14.43 (GP41)
/PGPIO42: J4.35, U14.44 (GP42)
/PGPIO43: J4.34, U14.45 (GP43)
/PGPIO44: J4.37, U14.46 (GP44)
/PGPIO45: J4.36, U14.47 (GP45)
/PGPIO46: J4.38, U14.49 (GP46)
/PRUN: S5.1, S5.3, S6.1, U14.56 (RUN)
/PS2/KB_CLK_5V: J7.5, U4.13 (B1)
/PS2/KB_DATA_5V: J7.1, U4.12 (B2)
/PS2/MS_CLK_5V: J7.6, U4.11 (B3)
/PS2/MS_DATA_5V: J7.2, U4.10 (B4)
/PSWCLK: J2.3, U14.55 (SWCLK)
/PSWDIO: J2.1, U14.52 (SWDIO)
/Power/D+: J6.6 (DP1), J6.8 (DP2), R19.2
/Power/D-: J6.5 (DN2), J6.7 (DN1), R18.2
/Power/DM: U2.6 (I/O1), U15.5 (2Y1)
/Power/DP: U2.4 (I/O2), U15.14 (1Y1)
/Power/VBUS_IN: C1.1, C2.1, C3.1, R9.2, S4.2, U1.7 (VIN)
/SHND: R116.2, S1.6, U19.12 (SHND)
/TC_DM: U14.53 (USB_DM), U15.3 (2Z)
/TC_DP: U14.54 (USB_DP), U15.13 (1Z)
/Tape In/LOAD_IN: S1.9, U17.6 (I=*C)
/Tape In/TAPE: C29.2, J12.2 (TIP)
/UM_SW: R72.2, S9.1, U15.10 (S0)
/USB Hub/DM1: R122.1, U13.7 (DM3)
/USB Hub/DM2: R124.1, U13.5 (DM2)
/USB Hub/DM3: R134.1, U13.3 (DM1)
/USB Hub/DM4: R136.1, U13.1 (DM0)
/USB Hub/DM_IN: U13.10 (DMU), U15.1 (2Y0)
/USB Hub/DP1: R121.1, U13.8 (DP3)
/USB Hub/DP2: R123.1, U13.6 (DP2)
/USB Hub/DP3: R133.1, U13.4 (DP1)
/USB Hub/DP4: R135.1, U13.2 (DP0)
/USB Hub/DP_IN: U13.11 (DPU), U15.12 (1Y0)
GND: C1.2, C2.2, C3.2, C6.1, C7.2, C8.2, C9.2, C10.2, C11.2, C12.2, C13.2, C14.2, C15.1, C16.1, C17.2, C18.2, C19.2, C20.2, C21.2, C22.2, C23.2, C24.2, C25.2, C26.2, C27.1, C30.2, C31.2, C32.2, C33.2, C34.2, C35.2, C39.1, C40.2, C42.2, C45.1, C46.2, C47.2, C48.1, C49.1, C50.2, C51.2, C52.2, C53.2, D1.2 (A), D5.2 (A), D6.2 (A), H5.2 (-), J1.2, J2.2, J3.2, J4.40, J5.2, J6.1 (GND), J6.12 (GND), J7.3, J8.2, J9.2 (G_D2), J9.5 (G_D1), J9.8 (G_D0), J9.11 (G_CLK), J9.17 (G_DDC/CEC), J9.20 (SHIELD1), J9.21 (SHIELD2), J9.22 (SHIELD3), J9.23 (SHIELD4), J10.2, J11.2, J12.1 (SLEEVE), J15.1 (SLEEVE), J16.8, J17.8, J18.6 (VSS), J18.SH (SHIELD), J19.4 (GND1), J19.8 (GND2), J19.SH (Shield), J20.0, J20.5, J20.6, J20.7, J20.8, J20.10, J21.4 (GND1), J21.8 (GND2), J21.SH (Shield), LD1.1 (K), LD4.1 (K), Q1.2 (E), R10.2, R11.2, R12.2, R13.1, R14.1, R15.1, R16.1, R36.1, R37.1, R42.1, R47.2, R55.2, R72.1, R80.1, R91.2, R93.2, R99.2, R100.1, R101.2, R103.2, R106.1, R114.1, R115.1, R117.1, R118.1, S1.12, S2.2, S2.4, S3.2, S3.3 (GND), S5.2, S5.4, S6.2, S6.3 (GND), S7.2, S7.3 (GND), S8.2, S8.4, S9.4 (MH1), S9.5 (MH2), U1.5 (GND), U1.9 (EP), U2.2 (GND), U3.1 (GND), U4.7 (GND), U5.1 (VSS), U5.24 (~A9), U6.7 (GND), U7.1 (VSS), U7.24 (~A9), U8.8 (GND), U8.13 (~OE), U9.8 (GND), U9.13 (~OE), U10.5 (GND), U11.1 (GND), U12.4 (VSS), U13.15 (GND), U13.16 (GND), U14.1 (GND), U14.18 (GND), U14.33 (GND), U14.48 (GND), U15.2 (2Y2), U15.4 (2Y3), U15.6 (~E), U15.7 (VEE), U15.8 (GND), U15.9 (S1), U15.11 (1Y3), U15.15 (1Y2), U16.2 (GND), U17.7 (VSS), U17.9 (D14), U17.11 (E), U17.13 (F), U18.4 (AGND), U19.2 (PGND), U19.11 (GND), U19.15 (PGND), U20.4 (V-), U21.4 (2Y3), U21.6 (~E), U21.7 (VEE), U21.8 (GND), U21.11 (1Y3)
GP25: R71.2, U14.26 (GP25)
unnamed: C4.2, R11.1
unnamed: C9.1, J6.2 (VBUS), J6.11 (VBUS), L2.2
unnamed: C28.1, R86.2
unnamed: C29.1, R87.2
unnamed: C31.1, R90.1, R94.2, R97.1
unnamed: C32.1, R92.1, R95.2, R96.1
unnamed: C36.2, R107.2
unnamed: C37.2, R108.2
unnamed: C38.2, R109.2
unnamed: C41.2, R112.2
unnamed: C43.1, R110.1, U20.7
unnamed: C44.1, R111.1, U20.1
unnamed: C5.2, D1.1 (K), L1.1, U1.1 (SW)
unnamed: D2.1 (K), S8.1, S8.3
unnamed: D3.1 (K), U9.6 (QG)
unnamed: C24.1, D4.1 (K), J9.18 (+5V)
unnamed: H5.1 (+), J8.1, U10.6 (VBAT)
unnamed: J5.1, S4.3
unnamed: J6.4 (CC1), R13.2
unnamed: J6.10 (CC2), R14.2
unnamed: J6.13 (SHIELD), R16.2
unnamed: J9.12 (CLKN), R65.1
unnamed: J9.10 (CLKP), R69.1
unnamed: J9.9 (D0N), R63.1
unnamed: J9.7 (D0P), R66.1
unnamed: J9.6 (D1N), R67.1
unnamed: J9.4 (D1P), R70.1
unnamed: J9.3 (D2N), R64.1
unnamed: J9.1 (D2P), R68.1
unnamed: J16.2, R119.2
unnamed: J17.2, R120.2
unnamed: J19.3 (D1+), R121.2
unnamed: J19.2 (D1-), R122.2
unnamed: J19.7 (D2+), R123.2
unnamed: J19.6 (D2-), R124.2
unnamed: J20.1, R125.2, R128.2
unnamed: J20.2, R126.2, R129.2
unnamed: J20.3, R127.2, R130.2
unnamed: J20.13, R131.1
unnamed: J20.14, R132.1
unnamed: J21.3 (D1+), R133.2
unnamed: J21.2 (D1-), R134.2
unnamed: J21.7 (D2+), R135.2
unnamed: J21.6 (D2-), R136.2
unnamed: LD1.2 (A), R20.1
unnamed: LD2.1 (K), R36.2
unnamed: LD3.1 (K), R37.2
unnamed: LD4.2 (A), R71.1
unnamed: C15.2, Q1.1 (B), R22.1, X1.1
unnamed: C16.2, Q1.3 (C), R22.2, R23.1, U6.3 (C), X1.2
unnamed: R18.1, U2.1 (I/O1)
unnamed: R19.1, U2.3 (I/O2)
unnamed: R42.2, R43.1, R44.1
unnamed: R44.2, R45.1, R46.1
unnamed: R46.2, R48.1, R49.1
unnamed: R49.2, R50.1, R51.1
unnamed: R51.2, R52.1, R53.1
unnamed: R53.2, R54.1, R56.1
unnamed: R56.2, R57.1, R58.1
unnamed: R73.2, R74.2, R81.2, R86.1
unnamed: R75.2, R81.1, R82.2
unnamed: R76.2, R82.1, R83.2
unnamed: R77.2, R83.1, R84.2
unnamed: R78.2, R84.1, R85.2
unnamed: R79.2, R80.2, R85.1
unnamed: S10.1 (A), U12.2 (SO/SIO)
unnamed: C5.1, U1.8 (BST)
unnamed: C4.1, U1.3 (COMP)
unnamed: R9.1, R10.1, U1.2 (EN)
unnamed: R15.2, R17.2, U1.4 (FB)
unnamed: R12.1, U1.6 (FREQ)
unnamed: U6.2 (D), U6.6 (~Q)
unnamed: U8.9 (QH'), U9.14 (SER)
unnamed: U13.12 (VD33), U13.14 (VD3)
unnamed: R87.1, R88.2, U17.1 (A)
unnamed: R89.1, U17.3 (B)
unnamed: U17.4 (H=*B), U17.5 (C)
unnamed: R88.1, R89.2, U17.2 (G-*A)
unnamed: C35.1, U18.7 (FLT)
unnamed: C33.1, C34.1, R98.1, U18.5 (VA)
unnamed: R107.1, U19.7 (INL)
unnamed: R112.1, U19.10 (INR)
unnamed: C40.1, U19.8 (VREF)
unnamed: C39.2, R105.1, R106.2, U20.3 (+), U20.5 (+)
unnamed: R109.1, R111.2, U20.2 (-)
unnamed: R108.1, R110.2, U20.6 (-)
unnamed: C42.1, C45.2, R105.2, R113.2, U20.8 (V+)
VBUS: C6.2, C7.1, C8.1, C11.1, C14.1, C17.1, C18.1, C19.1, C20.1, C21.1, C22.1, C26.1, C27.2, C46.1, C47.1, C48.2, C50.1, C51.1, C52.1, C53.1, D4.2 (A), J3.3, J7.4, J11.1, J16.6, J17.6, J19.1 (VBUS1), J19.5 (VBUS2), J21.1 (VBUS1), J21.5 (VBUS2), L1.2, L2.1, R17.1, R21.1, R23.2, R28.1, R29.2, R98.2, R113.1, R116.1, S1.7, S1.8, S9.2, U2.5 (VBUS), U3.3 (VI), U4.14 (VCCB), U5.28 (BC2), U5.40 (VCC), U6.1 (~R), U6.4 (~S), U6.14 (VCC), U7.28 (BC2), U7.40 (VCC), U8.10 (~SRCLR), U8.16 (VCC), U9.10 (~SRCLR), U9.16 (VCC), U13.13 (VDD5), U14.60 (VBUS), U15.16 (VCC), U19.4 (PVDD), U19.5 (MUTE), U19.6 (VDD), U19.13 (PVDD), U21.16 (VCC)
